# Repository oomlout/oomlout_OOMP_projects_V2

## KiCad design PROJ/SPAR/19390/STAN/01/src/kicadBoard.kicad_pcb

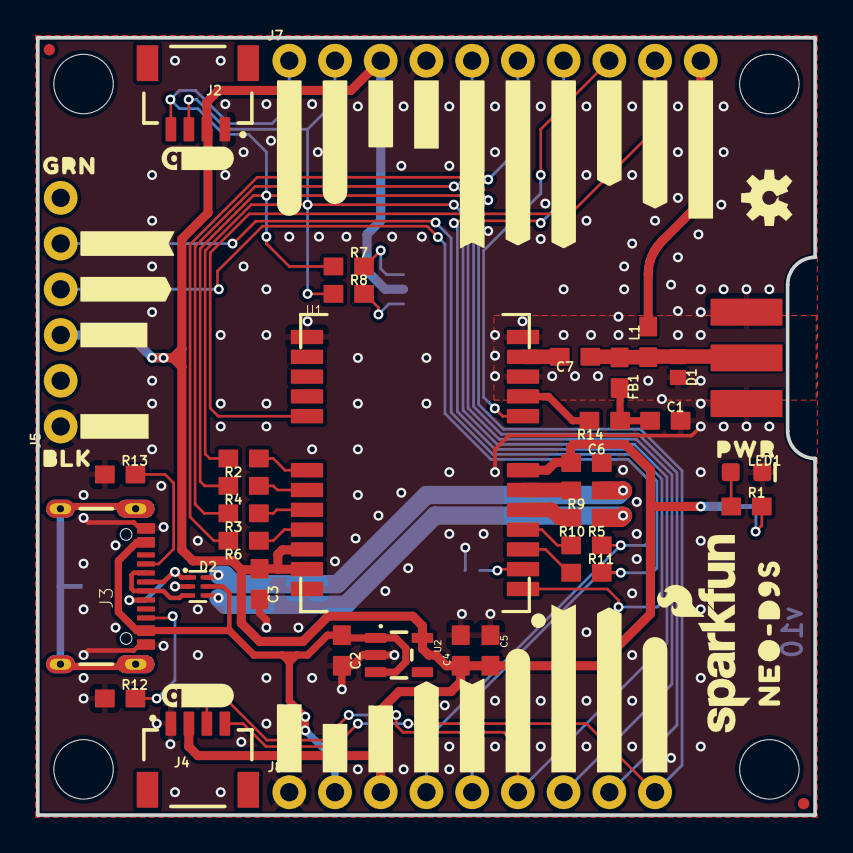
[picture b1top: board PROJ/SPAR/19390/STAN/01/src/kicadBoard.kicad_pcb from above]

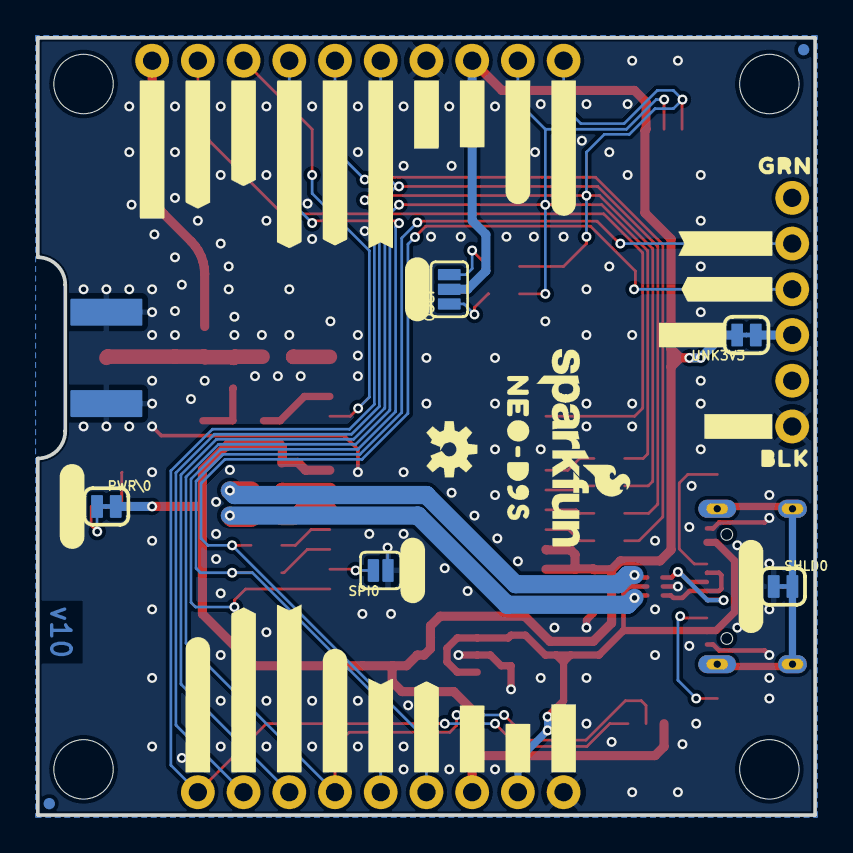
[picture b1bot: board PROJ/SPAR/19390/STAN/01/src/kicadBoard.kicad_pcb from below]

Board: 2 copper layers, 43.2 x 43.2 mm, 112 parts (39 on the bottom side), 38 nets.

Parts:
C1, C7: 47pF; 0603
C2, C3, C4, C6: 1.0uF; 0603
C5: 0.1uF; 0603
D1: PESD0402-0402; 0402
D2: PRTR5V0U2F; SOT886
FB1: 30Ω/1.8A; 0603
FRAME1: FRAME-LETTER; CREATIVE_COMMONS
I2C0: JUMPER-SMT_3_NO_SILK; SMT-JUMPER_3_NO_SILK
J1: ANTENNA-SMA-GROUNDEDEDGE_SMA; SMA-EDGE
J2, J4: Qwiic Right Angle; JST04_1MM_RA
J3: USB-C-16P-2LAYER-PADS
J5: 1X06_NO_SILK
J7: 1X10_NO_SILK
J8: 1X09_NO_SILK
JP21, JP61, JP71, JP81: FIDUCIALUFIDUCIAL; MICRO-FIDUCIAL
JP31, JP41, JP91, JP101: STAND-OFF
L1: DNP; 0603_NO-CREAM
LED1: RED; LED-0603
LOGO1, LOGO4: OSHW-LOGOS; OSHW-LOGO-S
LOGO2, LOGO3: SFE_LOGO_NAME_FLAME.1_INCH; SFE_LOGO_NAME_FLAME_.1
PWR\0: JUMPER-SMT_2_NC_TRACE_SILK; SMT-JUMPER_2_NC_TRACE_SILK
R1: 1k; 0603
R2, R3, R4, R5, R6, R11: 33; 0603
R7, R8: 2.2k; 0603
R9, R10: 27; 0603
R12, R13: 5.1k; 0603
R14: 10; 0603
SHLD0: JUMPER-SMT_2_NC_TRACE_SILK; SMT-JUMPER_2_NC_TRACE_SILK
SPI0: JUMPER-SMT_2_NO_SILK; SMT-JUMPER_2_NO_SILK
U1: U-BLOX_NEO-D9S-00B; NEO-M9N_M8T_M8U_D9S
U2: 3.3V; SOT23-5
U$1, U$2, U$3: #GND#0
U$4, U$5, U$6: #GND#1
U$7, U$8: #TXD2#0
U$9, U$10: #TXD2#3
U$11, U$12: #RXD2#0
U$13, U$15: #RXD2#3
U$14, U$38: QWIIC_4MM
U$16, U$17: BLK0
U$18, U$19: GRN0
U$20: #5V#0
U$21: #5V#6
U$22, U$23, U$56, U$57: #3V3#0
U$24, U$25: #3V3#4
U$26, U$27: #SDA##CS##0
U$28, U$29: #SDA##CS##1
U$30, U$31: #TXD1#POCI#0
U$32, U$33: #TXD1#POCI#2
U$34, U$35: #RXD1#PICO#0
U$36, U$37: #RXD1#PICO#2
U$39, U$40: #SCL#SCK#0
U$41, U$42: #SCL#SCK#1
U$43: ##SAFEBOOT##0
U$44: ##SAFEBOOT##1
U$45: ##RESET##0
U$46: ##RESET##1
U$47: #EXT_INT#0
U$48: #EXT_INT#1
U$49: PWR0
U$50: #PWR#0
U$51: #SPI#0
U$52: #I�C#0
U$53: #SHLD#0
U$54, U$55: NEO#D9S0
U$58: #ANT_PWR#0
U$59: #ANT_PWR#1
UNK3V3: JUMPER-SMT_2_NC_TRACE_SILK; SMT-JUMPER_2_NC_TRACE_SILK

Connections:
3.3V: C3.1, C4.1, C5.2, C6.1, I2C0.2, J2.2, J4.2, J7.3, J8.3, PWR\0.2, U1.7, U1.22, U1.23, U2.5, UNK3V3.2
5V: C2.1, D2.5, J3.VBUS1, J3.VBUS2, J8.2, U2.1, U2.3
ANT: C7.2, U1.11
ANT_PWR: J7.10, L1.2
ANT_VCC: C1.1, FB1.2, R14.1
D+: D2.6, R9.1
D-: D2.4, R10.1
D_SEL: SPI0.2, U1.2
EXT_INT: J7.9, U1.17
GND: C1.2, C2.2, C3.2, C4.2, C5.1, C6.2, D1.2, D2.2, J1.GND@0, J1.GND@1, J1.GND@2, J1.GND@3, J2.1, J3.GND, J3.GND2, J4.1, J5.1, J7.4, J8.1, LED1.C, R12.1, R13.1, SHLD0.1, SPI0.1, U1.10, U1.12, U1.13, U1.24, U2.2
unnamed: PWR\0.1, R1.2
unnamed: R3.1, U1.20
unnamed: R2.1, U1.18
unnamed: R4.1, U1.19
unnamed: I2C0.1, R8.2
unnamed: R6.1, U1.21
unnamed: J3.B5, R12.2
unnamed: I2C0.3, R7.2
unnamed: J3.A5, R13.2
unnamed: LED1.A, R1.1
unnamed: R9.2, U1.6
unnamed: R10.2, U1.5
unnamed: J5.3, UNK3V3.1
unnamed: R11.1, U1.3
unnamed: R5.1, U1.4
RXD1/PICO: J7.6, J8.8, R6.2
RXD2: J5.4, J8.4, R5.2
SCL/SCK: J2.4, J4.4, J7.1, J8.9, R4.2, R7.1
SDA/~CS: J2.3, J4.3, J7.2, J8.6, R2.2, R8.1
SHIELD: J3.SHLD1, J3.SHLD2, J3.SHLD3, J3.SHLD4, SHLD0.2
SMA: C7.1, D1.1, FB1.1, J1.SIG, L1.1
TXD1/POCI: J7.5, J8.7, R3.2
TXD2: J5.5, J8.5, R11.2
USB_D+: D2.1, J3.A6, J3.B6
USB_D-: D2.3, J3.A7, J3.B7
VCC_RF: R14.2, U1.9
~RESET: J7.8, U1.8
~SAFEBOOT: J7.7, U1.1

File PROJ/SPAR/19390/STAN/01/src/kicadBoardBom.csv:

"Id";"Designator";"Package";"Quantity";"Designation";"Supplier and ref";
1;"U$47";"#EXT_INT#0";1;"";;;
2;"R10,R9";"0603";2;"27";;;
3;"U$29,U$28";"#SDA##CS##1";2;"";;;
4;"U$34,U$35";"#RXD1#PICO#0";2;"";;;
5;"LED1";"LED-0603";1;"RED";;;
6;"J1";"SMA-EDGE";1;"ANTENNA-SMA-GROUNDEDEDGE_SMA";;;
7;"FRAME1";"CREATIVE_COMMONS";1;"FRAME-LETTER";;;
8;"U$4,U$6,U$5";"#GND#1";3;"";;;
9;"U$12,U$11";"#RXD2#0";2;"";;;
10;"C1,C7";"0603";2;"47pF";;;
11;"U$30,U$31";"#TXD1#POCI#0";2;"";;;
12;"U$2,U$1,U$3";"#GND#0";3;"";;;
13;"C3,C4,C6,C2";"0603";4;"1.0uF";;;
14;"J4,J2";"JST04_1MM_RA";2;"Qwiic Right Angle";;;
15;"U$36,U$37";"#RXD1#PICO#2";2;"";;;
16;"J7";"1X10_NO_SILK";1;"";;;
17;"U$32,U$33";"#TXD1#POCI#2";2;"";;;
18;"R6,R5,R4,R3,R2,R11";"0603";6;"33";;;
19;"U$45";"##RESET##0";1;"";;;
20;"U$8,U$7";"#TXD2#0";2;"";;;
21;"LOGO3,LOGO2";"SFE_LOGO_NAME_FLAME_.1";2;"SFE_LOGO_NAME_FLAME.1_INCH";;;
22;"FB1";"0603";1;"30Ω/1.8A";;;
23;"U$14,U$38";"QWIIC_4MM";2;"";;;
24;"R1";"0603";1;"1k";;;
25;"JP41,JP91,JP101,JP31";"STAND-OFF";4;"STAND-OFF";;;
26;"JP21,JP61,JP71,JP81";"MICRO-FIDUCIAL";4;"FIDUCIALUFIDUCIAL";;;
27;"U$16,U$17";"BLK0";2;"";;;
28;"R7,R8";"0603";2;"2.2k";;;
29;"R13,R12";"0603";2;"5.1k";;;
30;"U$26,U$27";"#SDA##CS##0";2;"";;;
31;"LOGO1,LOGO4";"OSHW-LOGO-S";2;"OSHW-LOGOS";;;
32;"U$25,U$24";"#3V3#4";2;"";;;
33;"D1";"0402";1;"PESD0402-0402";;;
34;"C5";"0603";1;"0.1uF";;;
35;"D2";"SOT886";1;"PRTR5V0U2F";;;
36;"J5";"1X06_NO_SILK";1;"";;;
37;"U$41,U$42";"#SCL#SCK#1";2;"";;;
38;"U$18,U$19";"GRN0";2;"";;;
39;"U$54,U$55";"NEO#D9S0";2;"";;;
40;"U$56,U$22,U$23,U$57";"#3V3#0";4;"";;;
41;"R14";"0603";1;"10";;;
42;"U2";"SOT23-5";1;"3.3V";;;
43;"U$20";"#5V#0";1;"";;;
44;"J3";"USB-C-16P-2LAYER-PADS";1;"";;;
45;"L1";"0603_NO-CREAM";1;"DNP";;;
46;"U$49";"PWR0";1;"";;;
47;"J8";"1X09_NO_SILK";1;"";;;
48;"U$39,U$40";"#SCL#SCK#0";2;"";;;
49;"U$58";"#ANT_PWR#0";1;"";;;
50;"U1";"NEO-M9N_M8T_M8U_D9S";1;"U-BLOX_NEO-D9S-00B";;;
51;"U$43";"##SAFEBOOT##0";1;"";;;
52;"PWR\0,SHLD0,UNK3V3";"SMT-JUMPER_2_NC_TRACE_SILK";3;"JUMPER-SMT_2_NC_TRACE_SILK";;;
53;"U$46";"##RESET##1";1;"";;;
54;"U$48";"#EXT_INT#1";1;"";;;
55;"U$10,U$9";"#TXD2#3";2;"";;;
56;"U$59";"#ANT_PWR#1";1;"";;;
57;"U$52";"#I�C#0";1;"";;;
58;"U$51";"#SPI#0";1;"";;;
59;"U$44";"##SAFEBOOT##1";1;"";;;
60;"U$50";"#PWR#0";1;"";;;
61;"U$13,U$15";"#RXD2#3";2;"";;;
62;"I2C0";"SMT-JUMPER_3_NO_SILK";1;"JUMPER-SMT_3_NO_SILK";;;
63;"U$21";"#5V#6";1;"";;;
64;"U$53";"#SHLD#0";1;"";;;
65;"SPI0";"SMT-JUMPER_2_NO_SILK";1;"JUMPER-SMT_2_NO_SILK";;;

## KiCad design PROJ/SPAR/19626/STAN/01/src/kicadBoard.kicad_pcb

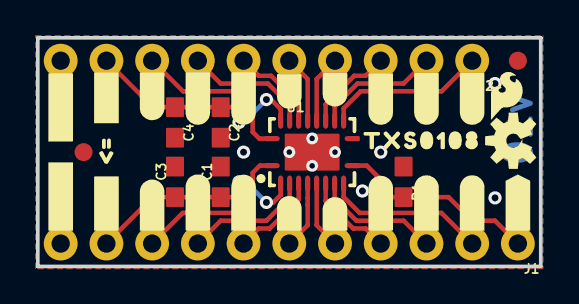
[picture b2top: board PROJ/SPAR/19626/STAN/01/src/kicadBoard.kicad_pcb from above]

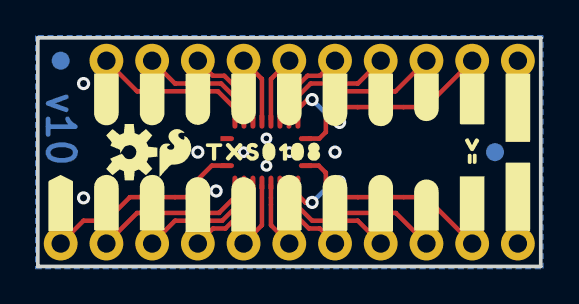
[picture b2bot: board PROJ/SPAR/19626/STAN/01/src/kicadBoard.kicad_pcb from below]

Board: 2 copper layers, 27.9 x 12.7 mm, 65 parts (28 on the bottom side), 20 nets.

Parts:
C1, C2: 0.1uF; 0603
C3, C4: 10uF; 0603
FD1, FD2, FD3, FD4: FIDUCIAL1X2; FIDUCIAL-1X2
FRAME1: FRAME-LETTER; CREATIVE_COMMONS
J1: 1X11_NO_SILK
J2: 1X10_NO_SILK
LOGO1, LOGO4: OSHW-LOGOS; OSHW-LOGO-S
LOGO2, LOGO3: SFE_LOGO_FLAME.1_INCH; SFE_LOGO_FLAME_.1
R1: 100k; 0603
U1: TXS0108; VFQFN-20
U$1, U$2, U$32, U$34: #GND#0
U$3, U$4: #VA#0
U$5: #A1#0
U$6: #A2#0
U$7: #A3#0
U$8: #4#0
U$9: #5#0
U$10: #A6#0
U$11: #A7#0
U$12: #A8#0
U$13: #B8#0
U$14: #B7#0
U$15: #B6#0
U$16: #4#6
U$17: #5#6
U$18: #B3#0
U$19: #B2#0
U$20: #B1#0
U$21: #OE#0
U$22, U$23: #VB#0
U$24: #A1#2
U$25: #A2#2
U$26: #A3#3
U$27: #A4#4
U$28: #A5#5
U$29: #A6#6
U$30: #A7#8
U$31: #A8#9
U$33, U$47: #0
U$35: #B8#9
U$36: #B7#9
U$37: #B6#9
U$38: #B5#9
U$39: #B4#9
U$40: #B3#9
U$41: #B2#9
U$42: #B1#9
U$43, U$44: TXS01080
U$45: #OE#1
U$46, U$48: V0

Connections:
A1: J1.9, U1.1
A2: J1.8, U1.3
A3: J1.7, U1.4
A4: J1.6, U1.5
A5: J1.5, U1.6
A6: J1.4, U1.7
A7: J1.3, U1.8
A8: J1.2, U1.9
B1: J2.8, U1.20
B2: J2.7, U1.18
B3: J2.6, U1.17
B4: J2.5, U1.16
B5: J2.4, U1.15
B6: J2.3, U1.14
B7: J2.2, U1.13
B8: J2.1, U1.12
GND: C1.2, C2.2, C3.2, C4.2, J1.11, J2.10, R1.1, U1.11, U1.EPAD
OE: J1.1, R1.2, U1.10
VCCA: C1.1, C3.1, J1.10, U1.2
VCCB: C2.1, C4.1, J2.9, U1.19

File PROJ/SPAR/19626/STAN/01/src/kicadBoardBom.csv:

"Id";"Designator";"Package";"Quantity";"Designation";"Supplier and ref";
1;"U$20";"#B1#0";1;"";;;
2;"J2";"1X10_NO_SILK";1;"";;;
3;"U$7";"#A3#0";1;"";;;
4;"LOGO1,LOGO4";"OSHW-LOGO-S";2;"OSHW-LOGOS";;;
5;"U$8";"#4#0";1;"";;;
6;"U$19";"#B2#0";1;"";;;
7;"U$9";"#5#0";1;"";;;
8;"U$15";"#B6#0";1;"";;;
9;"C2,C1";"0603";2;"0.1uF";;;
10;"U$18";"#B3#0";1;"";;;
11;"U$14";"#B7#0";1;"";;;
12;"U$5";"#A1#0";1;"";;;
13;"U$3,U$4";"#VA#0";2;"";;;
14;"U$44,U$43";"TXS01080";2;"";;;
15;"U$33,U$47";"#0";2;"";;;
16;"J1";"1X11_NO_SILK";1;"";;;
17;"U$21";"#OE#0";1;"";;;
18;"FD1,FD3,FD2,FD4";"FIDUCIAL-1X2";4;"FIDUCIAL1X2";;;
19;"U$46,U$48";"V0";2;"";;;
20;"U$11";"#A7#0";1;"";;;
21;"C4,C3";"0603";2;"10uF";;;
22;"U$12";"#A8#0";1;"";;;
23;"U$17";"#5#6";1;"";;;
24;"LOGO2,LOGO3";"SFE_LOGO_FLAME_.1";2;"SFE_LOGO_FLAME.1_INCH";;;
25;"R1";"0603";1;"100k";;;
26;"U$2,U$1,U$34,U$32";"#GND#0";4;"";;;
27;"FRAME1";"CREATIVE_COMMONS";1;"FRAME-LETTER";;;
28;"U1";"VFQFN-20";1;"TXS0108";;;
29;"U$6";"#A2#0";1;"";;;
30;"U$13";"#B8#0";1;"";;;
31;"U$10";"#A6#0";1;"";;;
32;"U$22,U$23";"#VB#0";2;"";;;
33;"U$16";"#4#6";1;"";;;
34;"U$35";"#B8#9";1;"";;;
35;"U$29";"#A6#6";1;"";;;
36;"U$30";"#A7#8";1;"";;;
37;"U$27";"#A4#4";1;"";;;
38;"U$41";"#B2#9";1;"";;;
39;"U$37";"#B6#9";1;"";;;
40;"U$25";"#A2#2";1;"";;;
41;"U$36";"#B7#9";1;"";;;
42;"U$38";"#B5#9";1;"";;;
43;"U$45";"#OE#1";1;"";;;
44;"U$24";"#A1#2";1;"";;;
45;"U$42";"#B1#9";1;"";;;
46;"U$39";"#B4#9";1;"";;;
47;"U$26";"#A3#3";1;"";;;
48;"U$31";"#A8#9";1;"";;;
49;"U$40";"#B3#9";1;"";;;
50;"U$28";"#A5#5";1;"";;;

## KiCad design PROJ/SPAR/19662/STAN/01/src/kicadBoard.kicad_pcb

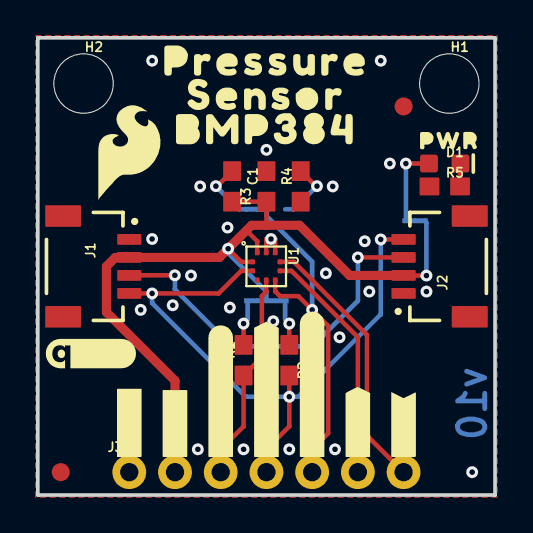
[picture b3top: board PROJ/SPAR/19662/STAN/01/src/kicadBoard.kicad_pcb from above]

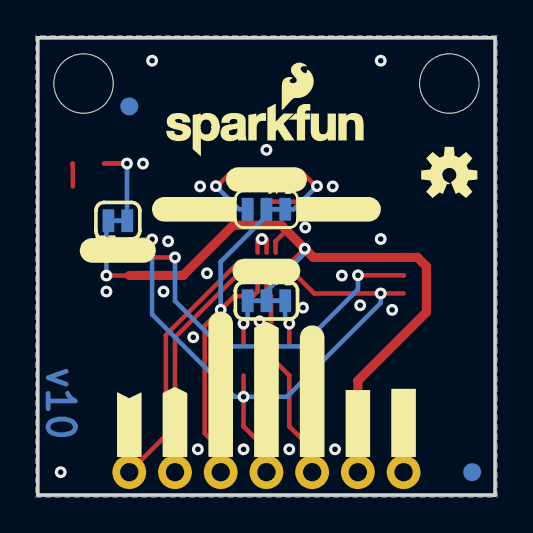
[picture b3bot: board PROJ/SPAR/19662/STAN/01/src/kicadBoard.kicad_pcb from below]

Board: 2 copper layers, 25.4 x 25.4 mm, 48 parts (19 on the bottom side), 13 nets.

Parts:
C1: 0.1uF; 0603
D1: RED; LED-0603
FD1, FD2, FD3, FD4: FIDUCIAL1X2; FIDUCIAL-1X2
FRAME1: FRAME-LETTER; CREATIVE_COMMONS
H1, H2: STAND-OFF
J1, J2: QWIIC_RIGHT_ANGLE; JST04_1MM_RA
J3: 1X07_NO_SILK
JP1: ADR; SMT-JUMPER_3_1-NC_TRACE_SILK
JP2: I2C; SMT-JUMPER_3_2-NC_TRACE_SILK
JP3: LED; SMT-JUMPER_2_NC_TRACE_SILK
LOGO1: OSHW-LOGOS; OSHW-LOGO-S
LOGO2: SFE_LOGO_FLAME.2_INCH; SFE_LOGO_FLAME_.2
LOGO3: QWIIC_LOGO_5MM; QWIIC_5MM
LOGO4: SFE_LOGO_NAME_FLAME.1_INCH; SFE_LOGO_NAME_FLAME_.1
R1, R2: 2.2k; 0603
R3, R4: 10k; 0603
R5: 1k; 0603
U1: BMP384; LGA-10
U$1, U$2: #GND#0
U$3, U$20: #3V3#0
U$4: #I2C#0
U$5, U$6: #SDI#SDA#0
U$7, U$8: #SCK#SCL#0
U$9, U$10: #SDO#ADR#0
U$11: #0X76#0
U$12: #0X77#0
U$13, U$14: #INT#0
U$15: PWR0
U$17: #ADR#0
U$19: #LED#0
U$21: PRESSURE0
U$25, U$28: ##CSB##0
U$26: SENSOR0
U$27: BMP3840

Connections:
GND: C1.2, J1.1, J2.1, J3.1, R4.1, R5.1, U1.3, U1.8, U1.9
INT: J3.7, U1.7
unnamed: JP1.3, R3.1
unnamed: JP1.1, R4.2
unnamed: JP2.1, R2.1
unnamed: JP2.3, R1.2
unnamed: D1.A, JP3.1
unnamed: D1.C, R5.2
SCK/SCL: J1.4, J2.4, J3.4, R2.2, U1.2
SDI/SDA: J1.3, J2.3, J3.3, R1.1, U1.4
SDO/ADR: J3.5, JP1.2, U1.5
VDD: C1.1, J1.2, J2.2, J3.2, JP2.2, JP3.2, R3.2, U1.1, U1.10
~CSB: J3.6, U1.6

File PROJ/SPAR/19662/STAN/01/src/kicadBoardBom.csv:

"Id";"Designator";"Package";"Quantity";"Designation";"Supplier and ref";
1;"D1";"LED-0603";1;"RED";;;
2;"R4,R3";"0603";2;"10k";;;
3;"FD3,FD1,FD2,FD4";"FIDUCIAL-1X2";4;"FIDUCIAL1X2";;;
4;"R2,R1";"0603";2;"2.2k";;;
5;"U$15";"PWR0";1;"";;;
6;"C1";"0603";1;"0.1uF";;;
7;"U$21";"PRESSURE0";1;"";;;
8;"J1,J2";"JST04_1MM_RA";2;"QWIIC_RIGHT_ANGLE";;;
9;"H1,H2";"STAND-OFF";2;"STAND-OFF";;;
10;"U$7,U$8";"#SCK#SCL#0";2;"";;;
11;"R5";"0603";1;"1k";;;
12;"U$5,U$6";"#SDI#SDA#0";2;"";;;
13;"U$20,U$3";"#3V3#0";2;"";;;
14;"U$27";"BMP3840";1;"";;;
15;"U$13,U$14";"#INT#0";2;"";;;
16;"LOGO3";"QWIIC_5MM";1;"QWIIC_LOGO_5MM";;;
17;"FRAME1";"CREATIVE_COMMONS";1;"FRAME-LETTER";;;
18;"U$1,U$2";"#GND#0";2;"";;;
19;"U$25,U$28";"##CSB##0";2;"";;;
20;"U$26";"SENSOR0";1;"";;;
21;"U1";"LGA-10";1;"BMP384";;;
22;"J3";"1X07_NO_SILK";1;"";;;
23;"U$9,U$10";"#SDO#ADR#0";2;"";;;
24;"LOGO2";"SFE_LOGO_FLAME_.2";1;"SFE_LOGO_FLAME.2_INCH";;;
25;"U$17";"#ADR#0";1;"";;;
26;"LOGO4";"SFE_LOGO_NAME_FLAME_.1";1;"SFE_LOGO_NAME_FLAME.1_INCH";;;
27;"JP2";"SMT-JUMPER_3_2-NC_TRACE_SILK";1;"I2C";;;
28;"U$4";"#I2C#0";1;"";;;
29;"U$19";"#LED#0";1;"";;;
30;"U$11";"#0X76#0";1;"";;;
31;"JP1";"SMT-JUMPER_3_1-NC_TRACE_SILK";1;"ADR";;;
32;"U$12";"#0X77#0";1;"";;;
33;"LOGO1";"OSHW-LOGO-S";1;"OSHW-LOGOS";;;
34;"JP3";"SMT-JUMPER_2_NC_TRACE_SILK";1;"LED";;;

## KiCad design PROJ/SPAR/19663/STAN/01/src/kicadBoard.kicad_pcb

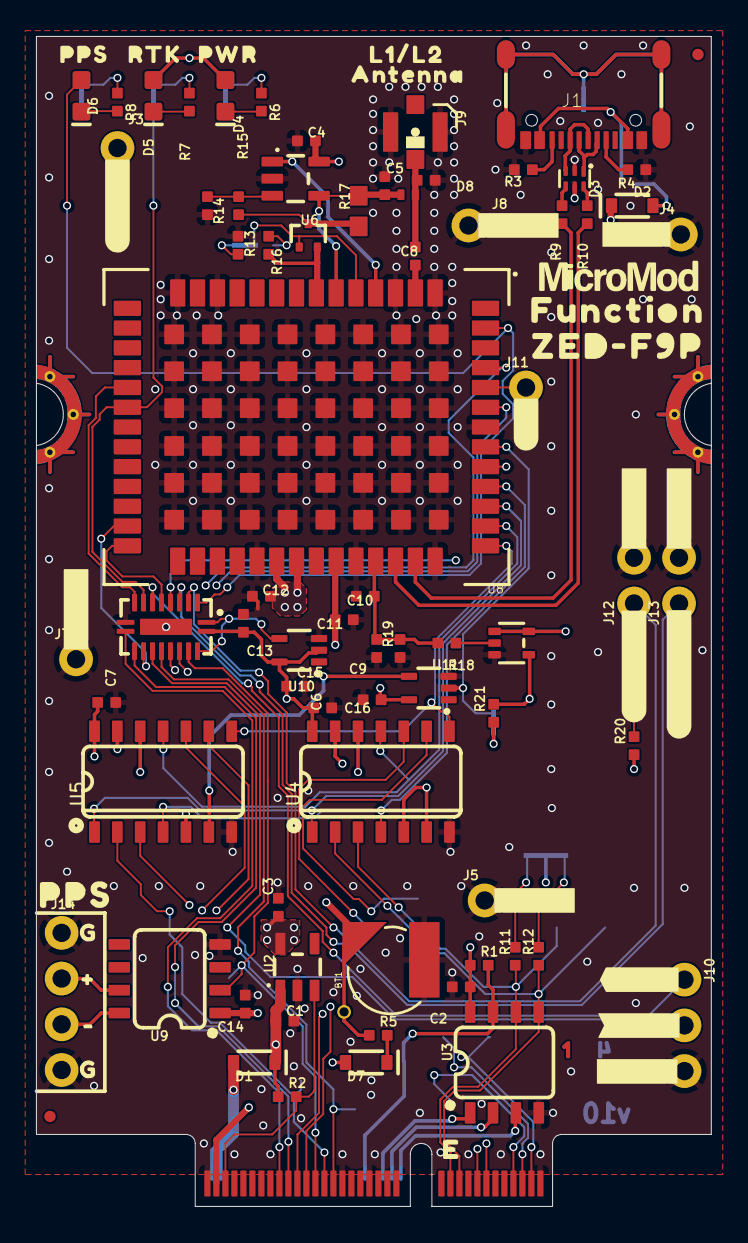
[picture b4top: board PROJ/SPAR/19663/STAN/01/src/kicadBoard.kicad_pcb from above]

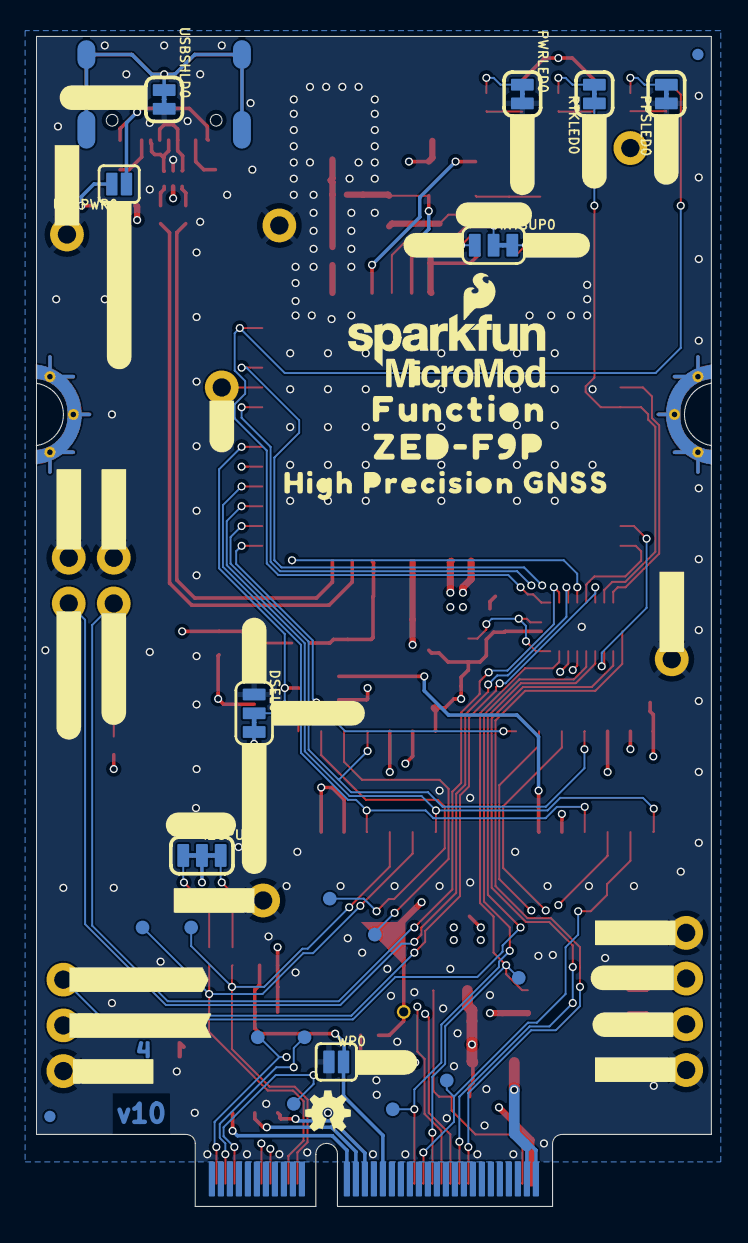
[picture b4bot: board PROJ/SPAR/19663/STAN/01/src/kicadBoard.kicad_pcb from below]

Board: 4 copper layers, 37.5 x 65.0 mm, 164 parts (56 on the bottom side), 78 nets.

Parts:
ANTSUP0: JUMPER-SMT_3_1-NC_TRACE_SILK; SMT-JUMPER_3_1-NC_TRACE_SILK
BT1: RELOWABLE_BATTERY_MS421R; MS421R_IV03E
C1, C3, C9, C12: 1.0uF; 0402-TIGHT
C2, C4, C6, C7, C10, C13, C14, C15, C16: 0.1uF; 0402-TIGHT
C5: 10nF; 0402-TIGHT
C8: 47pF; 0402-TIGHT
C11: 2.2uF; 0402-TIGHT
D1, D2: 3A/10V/280mV; SOD-323
D3: PRTR5V0U2F; SOT886
D4: RED; LED-0603
D5, D6: BLUE; LED-0603
D7: 0.5A/40V/420mV; SOD-323
D8: PESD0402-0402T; 0402-TIGHT
DSEL0: JUMPER-SMT_3_1-NC_TRACE_SILK; SMT-JUMPER_3_1-NC_TRACE_SILK
FD1, FD2, FD3, FD4: FIDUCIALUFIDUCIAL; FIDUCIAL-MICRO
FRAME1: FRAME-LEDGER; CREATIVE_COMMONS
I2CPUR0: JUMPER-SMT_3_2-NC_TRACE_SILK; SMT-JUMPER_3_2-NC_TRACE_SILK
J1: USB Female Type C Connector; USB-C-16P-4LAYER-ISOLATED
J2: MICROMOD_FUNCTION_STANDARD; M.2-CARD-E-22_FUNCTION_STANDARD
J3, J4, J5, J7, J8, J11: 1X01_NO_SILK
J6: 1X01_SMALL
J9: U.FL
J10: 455-1750-1-ND; 1X03_NO_SILK
J12, J13: 1X02_NO_SILK
J14: 1X04_NO_SILK
L1: 150nH; 0402_MURATA
LOGO1: SFE_LOGO_NAME_FLAMEBLANK; BLANK
LOGO2: SPECIAL_INSTRUCTIONS-ORDERING; ORDERING_INSTRUCTIONS
LOGO3: OSHW-LOGOMINI; OSHW-LOGO-MINI
LOGO4: SFE_LOGO_NAME_FLAME.1_INCH; SFE_LOGO_NAME_FLAME_.1
PPSLED0: JUMPER-SMT_2_NC_TRACE_SILK; SMT-JUMPER_2_NC_TRACE_SILK
PWRLED0: JUMPER-SMT_2_NC_TRACE_SILK; SMT-JUMPER_2_NC_TRACE_SILK
Q1: DMP21D0UT-7; SOT523
R1, R2, R13, R14, R20, R21: 10k; 0402-TIGHT
R3, R4: 5.1k; 0402-TIGHT
R5: 3.3K; 0402-TIGHT
R6, R15: 1k; 0402-TIGHT
R7, R8: 4.7k; 0402-TIGHT
R9, R10: 27; 0402-TIGHT
R11, R12: 2.2k; 0402-TIGHT
R16: 100k; 0402-TIGHT
R17: 10; 0603
R18: 220; 0402-TIGHT
R19: 470; 0402-TIGHT
RTKLED0: JUMPER-SMT_2_NC_TRACE_SILK; SMT-JUMPER_2_NC_TRACE_SILK
TP5, TP6, TP7, TP8, TP9, TP10, TP11, TP12, TP13, TP14: TEST-POINT3; PAD.03X.03
U1: NLAST4501DFT2G; SOT353
U2: 3.3V; SOT23-5
U3: EEPROM; SO08
U4, U5: 74LVC4066D_QUAD_BILATERAL_SWITCH; SO14
U6: OPA344; SOT23-5
U7: 74LVC541A; DHVQFN20
U8: U-BLOX_ZED-F9P; ZED-F9P
U9: FIN1017MX; SO08
U10, U11: SN74AUP1T04; SC-70-5_DCK
U$1: 40
U$2: #_RTCMTX#0
U$3: #TX2_#0
U$5, U$6, U$7, U$9, U$10, U$11, U$18, U$19, U$21, U$22, U$25, U$33, U$38, U$39: #_GND_#0
U$12: #_RTCMRX#0
U$13: #RX2_#0
U$14: ##RESET_##0
U$15: #_#RESET##0
U$16: #_EXTINT#0
U$17: #EXTINT_#0
U$23: #_I�C#SER#0
U$24: #SPI_#0
U$26, U$27: FUNCTION0
U$28: #_I�C#0
U$29: #_DSEL#0
U$30: #SUP#0
U$31: #RTK#0
U$32: #PWR#0
U$34: 10
U$35: 211
U$36: 3212
U$37, U$63: MICROMOD_LOGO_.35
U$40: PPS3
U$44: #PPS##2252
U$45: #PPS##2253
U$46, U$47: G2
U$48: #3
U$49: #4
U$50: #PPS#2254
U$51: PPS0
U$52: RTK0
U$54: #WP#0
U$62: #USBPWREN#10
U$64: #SHLD#12
U$68: #VZED#0
U$72: PWR0
U$73: #_DIS#0
U$74: #EN_#0
U$76: ##SB##9
U$80: ##SB##0
U$82: #GND#0
U$85: L1#L20
U$87: ANTENNA0
U$104: SFE_LOGO_FLAME_STOP_.1
U$106: HIGH_PRECISION_GNSS26
U$112, U$114: ZED#F9P0
USBPWR0: JUMPER-SMT_2_NO_SILK; SMT-JUMPER_2_NO_SILK
USBSHLD0: JUMPER-SMT_2_NC_TRACE_SILK; SMT-JUMPER_2_NC_TRACE_SILK
WP0: JUMPER-SMT_2_NO_SILK; SMT-JUMPER_2_NO_SILK

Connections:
3.3V: C2.1, C14.1, D7.A, J2.73, R1.1, U3.8, U9.1
5V: C1.1, D1.C, D2.C, R2.1, U2.1
A0: J2.36, U3.1
A1: J2.34, U3.2
A2: J2.32, U3.3
EWP: J2.40, R1.2, U3.7, WP0.2
EXTINT: J2.55, J13.1, U7.4
GEO_STAT: J2.59, U7.11
GND: BT1.-, C1.2, C2.2, C3.2, C4.2, C5.2, C6.2, C7.2, C9.2, C10.2, C11.2, C12.2, C13.2, C14.2, C15.2, C16.2, D3.2, D8.2, DSEL0.1, J1.GND, J1.GND2, J2.1, J2.33, J2.39, J2.45, J2.75, J2.GND1, J2.GND2, J2.GND3, J2.GND4, J2.GND5, J2.GND6, J4.1, J5.1, J7.1, J8.1, J9.1, J9.2, J10.3, J12.2, J13.2, J14.1, J14.4, PPSLED0.1, PWRLED0.2, R3.1, R4.1, R14.1, R16.1, R19.1, U1.3, U2.2, U3.4, U4.7, U5.7, U6.2, U7.10, U7.EPAD, U8.1, U8.3, U8.12, U8.14, U8.32, U8.37, U8.41, U8.48, U8.55, U8.56, U8.57, U8.58, U8.59, U8.60, U8.61, U8.62, U8.63, U8.64, U8.65, U8.66, U8.67, U8.68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
IO_~OE: U7.1, U7.19, U10.4
MM_PICO: J2.5, TP12.1, U5.10
MM_POCI: J2.7, TP13.1, U5.9
MM_RX: J2.15, TP7.1, U4.10
MM_SCK: J2.3, TP10.1, U5.3
MM_SCL: J2.21, R11.1, TP5.1, U3.6, U4.3
MM_SDA: J2.19, R12.1, TP6.1, U3.5, U4.2
MM_TX: J2.13, TP8.1, U4.9
MM_~CS: J2.49, TP11.1, U5.2
unnamed: ANTSUP0.1, R13.1
unnamed: ANTSUP0.3, R14.2
unnamed: J1.B5, R3.2
unnamed: J1.A5, R4.2
unnamed: DSEL0.3, R21.1
unnamed: I2CPUR0.3, R11.2
unnamed: C8.1, D8.1, J9.FEED, L1.2
unnamed: R7.1, RTKLED0.2
unnamed: I2CPUR0.1, R12.2
unnamed: Q1.1, R15.1, R17.1
unnamed: C9.1, C10.1, R18.2, R19.2, U8.38
unnamed: D2.A, USBPWR0.2
unnamed: PWRLED0.1, R6.1
unnamed: PPSLED0.2, R8.1
unnamed: D6.C, R8.2
unnamed: D5.C, R7.2
unnamed: D4.C, R6.2
unnamed: D7.C, R5.2
unnamed: R15.2, R16.2, U6.3
PPS: J2.51, TP9.1, U7.18, U9.2
PPS_DIFF_N: J14.3, U9.8
PPS_DIFF_P: J14.2, U9.7
PWR_EN: J2.71, R2.2, U2.3
RF_IN: C8.2, U8.2
RTK_STAT: J2.57, U7.12
RX2/RTCM: J10.1, U7.7
SHLD: J1.SHLD1, J1.SHLD2, J1.SHLD3, J1.SHLD4, J1.SHLD5, J1.SHLD6, J1.SHLD7, J1.SHLD8, USBSHLD0.1
TX2/RTCM: J10.2, U7.14
TX_READY: J2.47, TP14.1, U7.15
USBC_N: D3.1, J1.A7, J1.B7
USBC_P: D3.3, J1.A6, J1.B6
USB_N: D3.6, R10.1
USB_P: D3.4, R9.1
VIN: D1.A, J2.72, J2.74
V_BATT: BT1.+, C11.1, J6.P$1, R5.1, U8.36
V_RF: Q1.2, R13.2, U8.7
V_USB: D3.5, J1.VBUS1, J1.VBUS2, U1.1, U1.5, USBPWR0.1
V_ZED: C3.1, C4.1, C6.1, C7.1, C12.1, C13.1, C15.1, C16.1, D4.A, D5.A, I2CPUR0.2, J3.1, R20.1, R21.2, U1.4, U2.5, U4.14, U5.14, U6.5, U7.20, U8.33, U8.34, U10.2, U10.5, U11.5
ZED_ANT_DETECT: U6.1, U8.4
ZED_ANT_OFF: ANTSUP0.2, Q1.3, U8.5
ZED_ANT_~SHORT: C5.1, L1.1, R17.2, U6.4, U8.6
ZED_DSEL: DSEL0.2, U4.5, U4.6, U4.12, U4.13, U8.47, U11.2
ZED_EXTINT: U7.16, U8.51
ZED_GEO_STAT: U7.9, U8.19
ZED_PPS: D6.A, U7.2, U8.53
ZED_RTK_STAT: RTKLED0.1, U7.8, U8.20
ZED_RX2/RTCM: U7.13, U8.26
ZED_RX/PICO: U4.11, U5.11, U8.43
ZED_SCL/SCK: U4.4, U5.4, U8.45
ZED_SDA/~CS: U4.1, U5.1, U8.44
ZED_TX2/RTCM: U7.6, U8.27
ZED_TX/POCI: U4.8, U5.8, U8.42
ZED_TX_READY: U7.5, U8.46
ZED_USB_DET: R18.1, U1.2
ZED_USB_N: R10.2, U8.39
ZED_USB_P: R9.2, U8.40
ZED_~RESET: U7.17, U8.49
ZED_~SAFEBOOT: J11.1, U8.50
~RESET: J2.53, J12.1, R20.2, U7.3
~ZED_DSEL: U5.5, U5.6, U5.12, U5.13, U11.4

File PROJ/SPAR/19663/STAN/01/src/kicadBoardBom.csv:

"Id";"Designator";"Package";"Quantity";"Designation";"Supplier and ref";
1;"U$72";"PWR0";1;"";;;
2;"R18";"0402-TIGHT";1;"220";;;
3;"U$5,U$33,U$7,U$22,U$38,U$21,U$10,U$9,U$19,U$39,U$18,U$11,U$6,U$25";"#_GND_#0";14;"";;;
4;"U$49";"#4";1;"";;;
5;"R4,R3";"0402-TIGHT";2;"5.1k";;;
6;"U5,U4";"SO14";2;"74LVC4066D_QUAD_BILATERAL_SWITCH";;;
7;"U$14";"##RESET_##0";1;"";;;
8;"C3,C9,C1,C12";"0402-TIGHT";4;"1.0uF";;;
9;"C11";"0402-TIGHT";1;"2.2uF";;;
10;"C5";"0402-TIGHT";1;"10nF";;;
11;"FD3,FD1,FD4,FD2";"FIDUCIAL-MICRO";4;"FIDUCIALUFIDUCIAL";;;
12;"J9";"U.FL";1;"U.FL";;;
13;"U$48";"#3";1;"";;;
14;"D5,D6";"LED-0603";2;"BLUE";;;
15;"R15,R6";"0402-TIGHT";2;"1k";;;
16;"R2,R20,R14,R13,R1,R21";"0402-TIGHT";6;"10k";;;
17;"U11,U10";"SC-70-5_DCK";2;"SN74AUP1T04";;;
18;"R11,R12";"0402-TIGHT";2;"2.2k";;;
19;"D7";"SOD-323";1;"0.5A/40V/420mV";;;
20;"U$87";"ANTENNA0";1;"";;;
21;"U9";"SO08";1;"FIN1017MX";;;
22;"R16";"0402-TIGHT";1;"100k";;;
23;"U3";"SO08";1;"EEPROM";;;
24;"U$47,U$46";"G2";2;"";;;
25;"U$52";"RTK0";1;"";;;
26;"R9,R10";"0402-TIGHT";2;"27";;;
27;"LOGO1";"BLANK";1;"SFE_LOGO_NAME_FLAMEBLANK";;;
28;"U$17";"#EXTINT_#0";1;"";;;
29;"C15,C6,C2,C14,C13,C4,C7,C10,C16";"0402-TIGHT";9;"0.1uF";;;
30;"U$63,U$37";"MICROMOD_LOGO_.35";2;"";;;
31;"J7,J4,J5,J3,J8,J11";"1X01_NO_SILK";6;"";;;
32;"R19";"0402-TIGHT";1;"470";;;
33;"L1";"0402_MURATA";1;"150nH";;;
34;"J12,J13";"1X02_NO_SILK";2;"";;;
35;"J14";"1X04_NO_SILK";1;"";;;
36;"U$82";"#GND#0";1;"";;;
37;"U1";"SOT353";1;"NLAST4501DFT2G";;;
38;"U8";"ZED-F9P";1;"U-BLOX_ZED-F9P";;;
39;"J6";"1X01_SMALL";1;"";;;
40;"U$26,U$27";"FUNCTION0";2;"";;;
41;"U$34";"10";1;"";;;
42;"J1";"USB-C-16P-4LAYER-ISOLATED";1;"USB Female Type C Connector";;;
43;"R7,R8";"0402-TIGHT";2;"4.7k";;;
44;"R5";"0402-TIGHT";1;"3.3K";;;
45;"LOGO2";"ORDERING_INSTRUCTIONS";1;"SPECIAL_INSTRUCTIONS-ORDERING";;;
46;"U$40";"PPS3";1;"";;;
47;"Q1";"SOT523";1;"DMP21D0UT-7";;;
48;"U$68";"#VZED#0";1;"";;;
49;"U$36";"3212";1;"";;;
50;"U$85";"L1#L20";1;"";;;
51;"U$112,U$114";"ZED#F9P0";2;"";;;
52;"U$13";"#RX2_#0";1;"";;;
53;"FRAME1";"CREATIVE_COMMONS";1;"FRAME-LEDGER";;;
54;"U2";"SOT23-5";1;"3.3V";;;
55;"U7";"DHVQFN20";1;"74LVC541A";;;
56;"D2,D1";"SOD-323";2;"3A/10V/280mV";;;
57;"U$35";"211";1;"";;;
58;"U6";"SOT23-5";1;"OPA344";;;
59;"J10";"1X03_NO_SILK";1;"455-1750-1-ND";;;
60;"U$80";"##SB##0";1;"";;;
61;"R17";"0603";1;"10";;;
62;"U$51";"PPS0";1;"";;;
63;"C8";"0402-TIGHT";1;"47pF";;;
64;"BT1";"MS421R_IV03E";1;"RELOWABLE_BATTERY_MS421R";;;
65;"J2";"M.2-CARD-E-22_FUNCTION_STANDARD";1;"MICROMOD_FUNCTION_STANDARD";;;
66;"D4";"LED-0603";1;"RED";;;
67;"U$104";"SFE_LOGO_FLAME_STOP_.1";1;"";;;
68;"U$3";"#TX2_#0";1;"";;;
69;"D8";"0402-TIGHT";1;"PESD0402-0402T";;;
70;"D3";"SOT886";1;"PRTR5V0U2F";;;
71;"U$24";"#SPI_#0";1;"";;;
72;"TP13,TP7,TP5,TP8,TP6,TP10,TP12,TP9,TP14,TP11";"PAD.03X.03";10;"TEST-POINT3";;;
73;"LOGO4";"SFE_LOGO_NAME_FLAME_.1";1;"SFE_LOGO_NAME_FLAME.1_INCH";;;
74;"LOGO3";"OSHW-LOGO-MINI";1;"OSHW-LOGOMINI";;;
75;"PWRLED0,PPSLED0,USBSHLD0,RTKLED0";"SMT-JUMPER_2_NC_TRACE_SILK";4;"JUMPER-SMT_2_NC_TRACE_SILK";;;
76;"U$1";"40";1;"";;;
77;"ANTSUP0,DSEL0";"SMT-JUMPER_3_1-NC_TRACE_SILK";2;"JUMPER-SMT_3_1-NC_TRACE_SILK";;;
78;"U$16";"#_EXTINT#0";1;"";;;
79;"U$29";"#_DSEL#0";1;"";;;
80;"U$62";"#USBPWREN#10";1;"";;;
81;"U$50";"#PPS#2254";1;"";;;
82;"U$106";"HIGH_PRECISION_GNSS26";1;"";;;
83;"U$31";"#RTK#0";1;"";;;
84;"U$64";"#SHLD#12";1;"";;;
85;"U$30";"#SUP#0";1;"";;;
86;"I2CPUR0";"SMT-JUMPER_3_2-NC_TRACE_SILK";1;"JUMPER-SMT_3_2-NC_TRACE_SILK";;;
87;"U$2";"#_RTCMTX#0";1;"";;;
88;"U$76";"##SB##9";1;"";;;
89;"USBPWR0,WP0";"SMT-JUMPER_2_NO_SILK";2;"JUMPER-SMT_2_NO_SILK";;;
90;"U$45";"#PPS##2253";1;"";;;
91;"U$73";"#_DIS#0";1;"";;;
92;"U$44";"#PPS##2252";1;"";;;
93;"U$23";"#_I�C#SER#0";1;"";;;
94;"U$15";"#_#RESET##0";1;"";;;
95;"U$32";"#PWR#0";1;"";;;
96;"U$54";"#WP#0";1;"";;;
97;"U$28";"#_I�C#0";1;"";;;
98;"U$74";"#EN_#0";1;"";;;
99;"U$12";"#_RTCMRX#0";1;"";;;

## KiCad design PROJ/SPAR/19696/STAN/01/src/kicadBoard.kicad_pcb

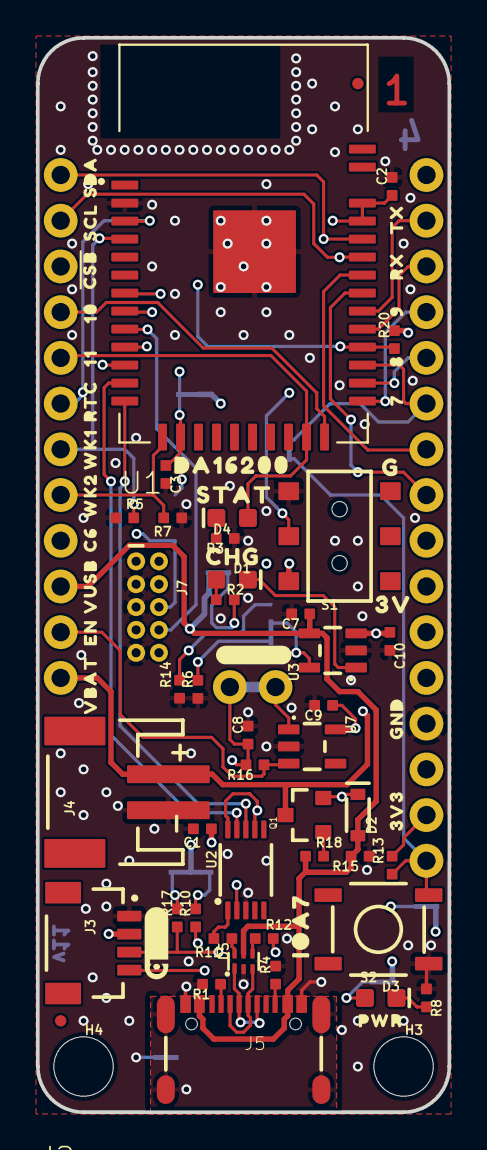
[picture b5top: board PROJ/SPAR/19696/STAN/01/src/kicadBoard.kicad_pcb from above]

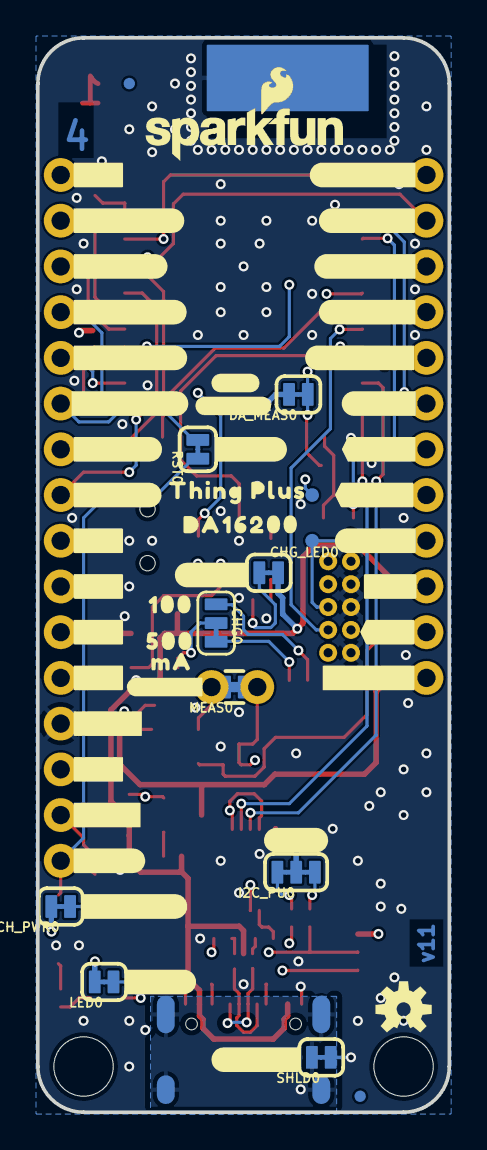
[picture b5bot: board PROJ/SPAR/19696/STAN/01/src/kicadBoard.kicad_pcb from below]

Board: 4 copper layers, 22.9 x 59.7 mm, 133 parts (57 on the bottom side), 53 nets.

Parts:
C1, C2, C3: 0.1uF; 0402-TIGHT
C7, C10: 4.7uF; 0402-TIGHT
C8: 1.0uF; 0402-TIGHT
C9: 2.2uF; 0402-TIGHT
CHG0: JUMPER-SMT_3_1-NC_TRACE_SILK; SMT-JUMPER_3_1-NC_TRACE_SILK
CHG_LED0: JUMPER-SMT_2_NC_TRACE_SILK; SMT-JUMPER_2_NC_TRACE_SILK
CH_PWR0: JUMPER-SMT_2_NC_TRACE_SILK; SMT-JUMPER_2_NC_TRACE_SILK
D1: Yellow; LED-0603
D2: 1A/23V/620mV; SOD-323
D3: RED; LED-0603
D4: BLUE; LED-0603
D5: PRTR5V0U2F; SOT886
DA_MEAS0: JUMPER-SMT_2_NC_TRACE_SILK; SMT-JUMPER_2_NC_TRACE_SILK
FD1, FD2, FD3, FD4: FIDUCIALUFIDUCIAL; FIDUCIAL-MICRO
FRAME1: FRAME-LEDGER; CREATIVE_COMMONS
GPIOC7: TEST-POINT3; PAD.03X.03
H3, H4: STAND-OFF
I2C_PU0: JUMPER-SMT_3_2-NC_TRACE_SILK; SMT-JUMPER_3_2-NC_TRACE_SILK
J2: THING_PLUS
J3: Qwiic; JST04_1MM_RA
J4: JST-2-SMD
J5: USB C; USB-C-16P-4LAYER-ISOLATED
J7: CORTEX_JTAG_DEBUG_PTH_NS; 2X5-PTH-1.27MM-NO_SILK
LED0: JUMPER-SMT_2_NC_TRACE_SILK; SMT-JUMPER_2_NC_TRACE_SILK
LOGO1: OSHW-LOGOS; OSHW-LOGO-S
LOGO2: SFE_LOGO_NAME_FLAME.1_INCH; SFE_LOGO_NAME_FLAME_.1
MEAS0: JUMPER-COMBO_2_NC_TRACE; COMBO-JUMPER_2_NC_TRACE
Q1: 20V/4.2A/52mΩ/1.4W; SOT23-3
R1, R4: 5.1k; 0402-TIGHT
R2, R3, R8: 1k; 0402-TIGHT
R5, R7: 4.7k; 0402-TIGHT
R6: 2.0K; 0402-TIGHT
R10, R17: 2.2k; 0402-TIGHT
R11, R12: 27; 0402-TIGHT
R13, R14, R15, R16, R20: 10k; 0402-TIGHT
R18: 100; 0402-TIGHT
RST0: JUMPER-SMT_2_NC_TRACE_SILK; SMT-JUMPER_2_NC_TRACE_SILK
S1: SWITCH_DPDT_SMD_AYZ0202
S2: MOMENTARY-SWITCH-SPST-SMD-5.2MM-TALL; TACTILE_SWITCH_SMD_5.2MM
SHLD0: JUMPER-SMT_2_NC_TRACE_SILK; SMT-JUMPER_2_NC_TRACE_SILK
TMS0: TEST-POINT3; PAD.03X.03
U1: DA16200MOD; XCVR_DA16200MOD-AAC4WA32
U2: CH340E_MSOP10; MSOP10
U3: MCP73831; SOT23-5
U7: XC6222B331MR-G; SOT23-5
U$1: STAT0
U$2: CHG0
U$3: #MEAS_#0
U$4: G0
U$5, U$43: ##RST##0
U$6: #VU#0
U$7: #IOA10#0
U$8, U$29: #MEAS#0
U$9: 3V0
U$10: #CH340#0
U$11: #0#SDA#0
U$12: #1#SCL#0
U$13: IOA7_0
U$14, U$15, U$18, U$19, U$20, U$40: #NC#0
U$16: PWR0
U$17: #DA#0
U$21: 5000
U$22: 1000
U$23: MA0
U$24: SDA0
U$25: SCL0
U$26: #CSB#0
U$27: #4#TXO#0
U$28: 110
U$30: #VBAT#0
U$31: ORDERING_INSTRUCTIONS
U$32: 100
U$33: RTC0
U$34: WK10
U$35: WK20
U$36: #5#RXI#0
U$37: EN0
U$38: VUSB0
U$39: VBAT0
U$41: TX0
U$42: RX0
U$44: 90
U$45: 80
U$47: 70
U$50: #GND#0
U$51: #3V3#0
U$53: #EN#0
U$55: GND0
U$56: THING_PLUS0
U$57: 3V30
U$59: #CHG#0
U$60: #IOC6#0
U$62: #6##CSB##0
U$63: #11#LED#0
U$64: QWIIC_4MM
U$65: C60
U$66: #9#POCI#0
U$67: #8#PICO#0
U$68: #7#SCLK#0
U$69: #2#A2#0
U$70: #3#A3#0
U$71: #WK2#0
U$72: #WK1#0
U$73: #RTC#0
U$80, U$81: DA162000
U$82: #I�C#0
U$84: #LED#0
U$85: #SHLD#0

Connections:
3.3V: C1.1, C9.1, CH_PWR0.2, DA_MEAS0.2, I2C_PU0.2, J2.27, J3.2, J7.1, LED0.2, R13.2, R20.2, S1.1, U7.5
A_CH2: J2.19, U1.31
A_CH3: J2.20, U1.30
EN: J2.11, R16.1, U7.3
GND: C1.2, C2.2, C3.2, C7.2, C8.2, C9.2, C10.2, D5.2, J2.25, J3.1, J4.1, J5.GND, J5.GND2, J7.3, J7.5, J7.9, R1.2, R3.1, R4.2, R5.1, R6.1, R7.1, R8.1, R14.1, R15.1, S1.3, S2.1, SHLD0.1, U1.2, U1.ANT_GND, U1.GND, U2.3, U3.2, U7.2
GPIOA10: J2.4, U1.23
GPIOC6: J2.9, J7.10, U1.11
GPIOC7: GPIOC7.1, J7.6, U1.10
GPIOC8: J7.8, U1.9
HDR_RTC_WAKE2: J2.8, R7.2, U1.14
I2C_SCL: J2.2, J3.4, R10.1, U1.32
I2C_SDA: J2.1, J3.3, R17.1, U1.33
unnamed: D4.C, R3.2
unnamed: I2C_PU0.3, R10.2
unnamed: I2C_PU0.1, R17.2
unnamed: D3.A, LED0.1
unnamed: D5.1, J5.A6, J5.B6
unnamed: D5.3, J5.A7, J5.B7
unnamed: D3.C, R8.2
unnamed: C2.1, C3.1, DA_MEAS0.1, U1.15, U1.34, U1.35
unnamed: D1.C, U3.1
unnamed: CHG0.3, R6.2
unnamed: J5.A5, R1.1
unnamed: J5.B5, R4.1
unnamed: D5.6, R11.1
unnamed: CHG0.2, U3.5
unnamed: C8.1, D2.C, MEAS0.1, MEAS0.3, Q1.2, R16.2
unnamed: D5.4, R12.1
unnamed: D1.A, R2.1
unnamed: R11.2, U2.1
unnamed: R12.2, U2.2
unnamed: CHG0.1, R14.2
unnamed: Q1.1, R18.2
unnamed: MEAS0.2, MEAS0.4, U7.1
unnamed: CHG_LED0.1, R2.2
unnamed: J5.SHLD1, J5.SHLD2, J5.SHLD3, J5.SHLD4, J5.SHLD5, J5.SHLD6, J5.SHLD7, J5.SHLD8, SHLD0.2
unnamed: CH_PWR0.1, U2.7, U2.10
RTC_PWR_KEY: J2.6, S1.2, U1.3
RTC_WAKE1: J2.7, R5.2, U1.4
SPI_CSB: J2.3, R20.1, U1.27
SPI_PICO: J2.17, U1.25
SPI_POCI: J2.16, U1.24
STAT_LED: D4.A, J2.5, U1.22
TCLK: J7.4, U1.8
TMS: J7.2, TMS0.1, U1.7
U0RXI: U1.13, U2.8
U0TXO: U1.12, U2.9
U1RXI: J2.15, U1.28
U1TXO: J2.14, U1.29
V_BATT: C10.1, J2.12, J4.2, Q1.3, U3.3
V_USB: C7.1, CHG_LED0.2, D2.A, D5.5, J2.10, J5.VBUS1, J5.VBUS2, R15.2, R18.1, U3.4
~RESET: J2.28, R13.1, RST0.1, S2.3
~RESET/SPI_CLK: J2.18, RST0.2, U1.26

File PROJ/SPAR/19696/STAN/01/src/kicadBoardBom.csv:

"Id";"Designator";"Package";"Quantity";"Designation";"Supplier and ref";
1;"FRAME1";"CREATIVE_COMMONS";1;"FRAME-LEDGER";;;
2;"J3";"JST04_1MM_RA";1;"Qwiic";;;
3;"S2";"TACTILE_SWITCH_SMD_5.2MM";1;"MOMENTARY-SWITCH-SPST-SMD-5.2MM-TALL";;;
4;"U1";"XCVR_DA16200MOD-AAC4WA32";1;"DA16200MOD";;;
5;"U$35";"WK20";1;"";;;
6;"U$37";"EN0";1;"";;;
7;"J5";"USB-C-16P-4LAYER-ISOLATED";1;"USB C";;;
8;"U$4";"G0";1;"";;;
9;"C2,C3,C1";"0402-TIGHT";3;"0.1uF";;;
10;"R7,R5";"0402-TIGHT";2;"4.7k";;;
11;"R3,R8,R2";"0402-TIGHT";3;"1k";;;
12;"R17,R10";"0402-TIGHT";2;"2.2k";;;
13;"U$64";"QWIIC_4MM";1;"";;;
14;"U$34";"WK10";1;"";;;
15;"C10,C7";"0402-TIGHT";2;"4.7uF";;;
16;"S1";"SWITCH_DPDT_SMD_AYZ0202";1;"";;;
17;"U$2";"CHG0";1;"";;;
18;"D1";"LED-0603";1;"Yellow";;;
19;"R11,R12";"0402-TIGHT";2;"27";;;
20;"R13,R14,R15,R20,R16";"0402-TIGHT";5;"10k";;;
21;"U$41";"TX0";1;"";;;
22;"J2";"THING_PLUS";1;"THING_PLUS";;;
23;"C9";"0402-TIGHT";1;"2.2uF";;;
24;"U7";"SOT23-5";1;"XC6222B331MR-G";;;
25;"U$9";"3V0";1;"";;;
26;"U$38";"VUSB0";1;"";;;
27;"U$1";"STAT0";1;"";;;
28;"R4,R1";"0402-TIGHT";2;"5.1k";;;
29;"D5";"SOT886";1;"PRTR5V0U2F";;;
30;"J7";"2X5-PTH-1.27MM-NO_SILK";1;"CORTEX_JTAG_DEBUG_PTH_NS";;;
31;"H4,H3";"STAND-OFF";2;"STAND-OFF";;;
32;"U$25";"SCL0";1;"";;;
33;"R6";"0402-TIGHT";1;"2.0K";;;
34;"FD1,FD2,FD4,FD3";"FIDUCIAL-MICRO";4;"FIDUCIALUFIDUCIAL";;;
35;"U$32";"100";1;"";;;
36;"U$42";"RX0";1;"";;;
37;"U$39";"VBAT0";1;"";;;
38;"D2";"SOD-323";1;"1A/23V/620mV";;;
39;"U$55";"GND0";1;"";;;
40;"Q1";"SOT23-3";1;"20V/4.2A/52mΩ/1.4W";;;
41;"D4";"LED-0603";1;"BLUE";;;
42;"D3";"LED-0603";1;"RED";;;
43;"U$65";"C60";1;"";;;
44;"J4";"JST-2-SMD";1;"";;;
45;"C8";"0402-TIGHT";1;"1.0uF";;;
46;"U$26";"#CSB#0";1;"";;;
47;"U$8,U$29";"#MEAS#0";2;"";;;
48;"U$24";"SDA0";1;"";;;
49;"U$13";"IOA7_0";1;"";;;
50;"U3";"SOT23-5";1;"MCP73831";;;
51;"U$16";"PWR0";1;"";;;
52;"U$57";"3V30";1;"";;;
53;"U$33";"RTC0";1;"";;;
54;"U$45";"80";1;"";;;
55;"R18";"0402-TIGHT";1;"100";;;
56;"U2";"MSOP10";1;"CH340E_MSOP10";;;
57;"U$47";"70";1;"";;;
58;"U$81,U$80";"DA162000";2;"";;;
59;"U$28";"110";1;"";;;
60;"U$31";"ORDERING_INSTRUCTIONS";1;"";;;
61;"U$44";"90";1;"";;;
62;"U$69";"#2#A2#0";1;"";;;
63;"DA_MEAS0,CH_PWR0,SHLD0,CHG_LED0,LED0,RST0";"SMT-JUMPER_2_NC_TRACE_SILK";6;"JUMPER-SMT_2_NC_TRACE_SILK";;;
64;"U$82";"#I�C#0";1;"";;;
65;"U$23";"MA0";1;"";;;
66;"U$22";"1000";1;"";;;
67;"U$84";"#LED#0";1;"";;;
68;"U$60";"#IOC6#0";1;"";;;
69;"U$40,U$14,U$19,U$18,U$15,U$20";"#NC#0";6;"";;;
70;"U$67";"#8#PICO#0";1;"";;;
71;"U$17";"#DA#0";1;"";;;
72;"U$50";"#GND#0";1;"";;;
73;"TMS0,GPIOC7";"PAD.03X.03";2;"TEST-POINT3";;;
74;"LOGO2";"SFE_LOGO_NAME_FLAME_.1";1;"SFE_LOGO_NAME_FLAME.1_INCH";;;
75;"U$70";"#3#A3#0";1;"";;;
76;"U$27";"#4#TXO#0";1;"";;;
77;"U$71";"#WK2#0";1;"";;;
78;"MEAS0";"COMBO-JUMPER_2_NC_TRACE";1;"JUMPER-COMBO_2_NC_TRACE";;;
79;"U$72";"#WK1#0";1;"";;;
80;"U$62";"#6##CSB##0";1;"";;;
81;"I2C_PU0";"SMT-JUMPER_3_2-NC_TRACE_SILK";1;"JUMPER-SMT_3_2-NC_TRACE_SILK";;;
82;"U$53";"#EN#0";1;"";;;
83;"U$51";"#3V3#0";1;"";;;
84;"U$43,U$5";"##RST##0";2;"";;;
85;"U$59";"#CHG#0";1;"";;;
86;"U$6";"#VU#0";1;"";;;
87;"U$10";"#CH340#0";1;"";;;
88;"CHG0";"SMT-JUMPER_3_1-NC_TRACE_SILK";1;"JUMPER-SMT_3_1-NC_TRACE_SILK";;;
89;"U$12";"#1#SCL#0";1;"";;;
90;"U$63";"#11#LED#0";1;"";;;
91;"U$68";"#7#SCLK#0";1;"";;;
92;"U$11";"#0#SDA#0";1;"";;;
93;"U$56";"THING_PLUS0";1;"";;;
94;"U$36";"#5#RXI#0";1;"";;;
95;"LOGO1";"OSHW-LOGO-S";1;"OSHW-LOGOS";;;
96;"U$66";"#9#POCI#0";1;"";;;
97;"U$7";"#IOA10#0";1;"";;;
98;"U$73";"#RTC#0";1;"";;;
99;"U$21";"5000";1;"";;;
100;"U$3";"#MEAS_#0";1;"";;;
101;"U$85";"#SHLD#0";1;"";;;
102;"U$30";"#VBAT#0";1;"";;;

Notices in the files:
parts and their libraries:
RELEASED UNDER THE CREATIVE COMMONS ATTRIBUTION SHARE-ALIKE 4.0 LICENSE
HTTPS://CREATIVECOMMONS.ORG/LICENSES/BY-SA/4.0
